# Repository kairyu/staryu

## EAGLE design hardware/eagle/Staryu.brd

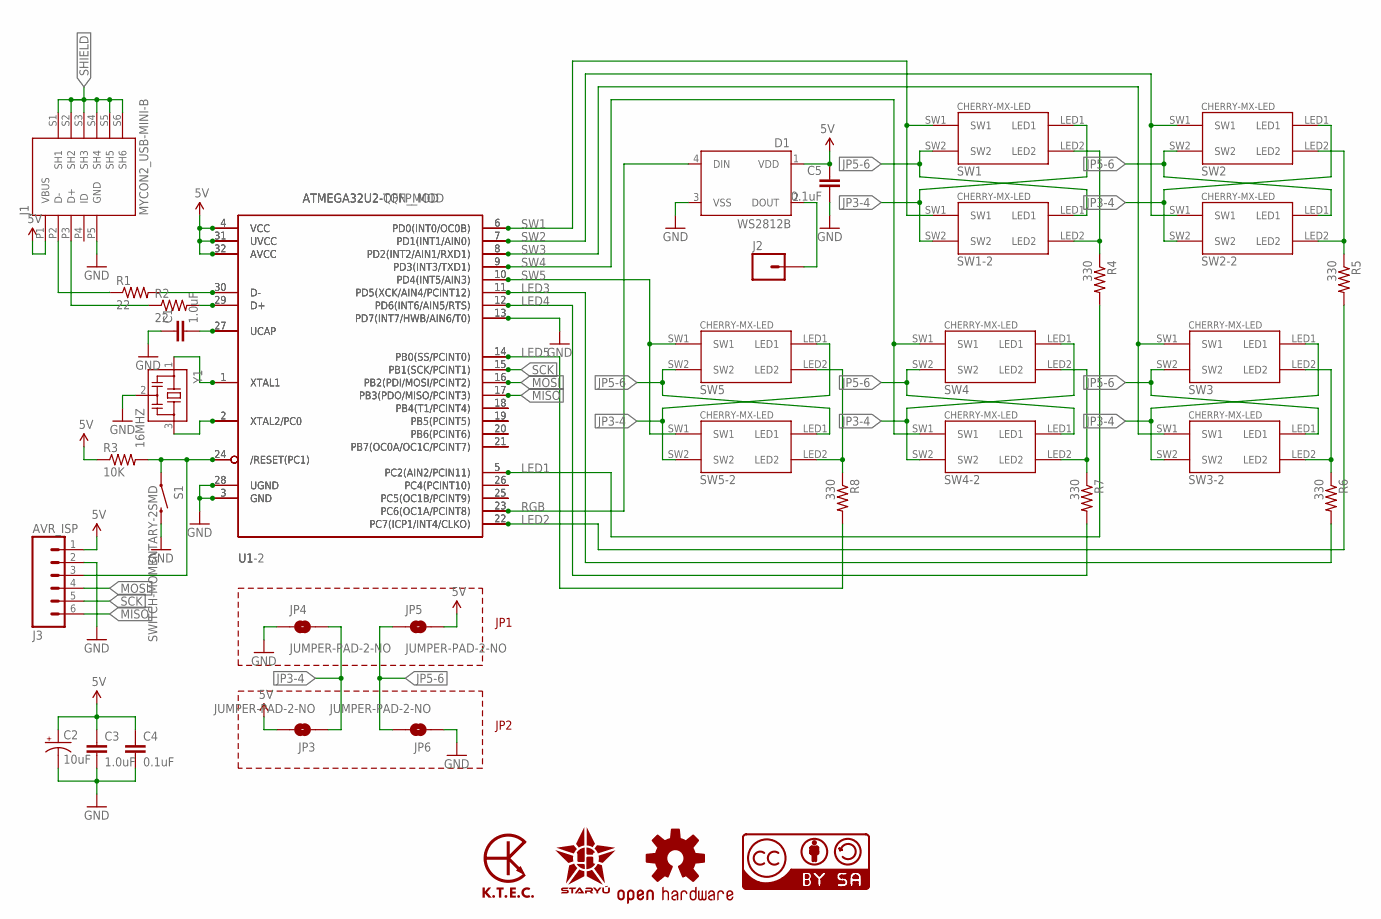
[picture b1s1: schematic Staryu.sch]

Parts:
C1, C3: 1.0uF; 0805-CAP
C2: 10uF; EIA3216
C4, C5: 0.1uF; 0805
D1: WS2812B; WS2812B_NOSILK
J1: MYCON2_USB-MINI-B; CON2_USB_MICRO_B_AT
J2: M01PTH_NO_SILK_YES_STOP; 1X01_NO_SILK
J3: AVR_ISP; 1X06_NO_SILK
JP3, JP4, JP5, JP6: JUMPER-PAD-2-NO; PAD-JUMPER-2-NO_NO_SILK
LOGO1: K.T.E.C._LOGO3_COPPER_EXP_S; K.T.E.C._LOGO3_COPPER_EXPOSED_S
LOGO2: STARYU_LOGO
LOGO3: OSHW_LOGOM_EXP; OSHW_LOGO_COPPER_EXPOSED_M
LOGO4: CC-BY-SANIX; CC-BY-SA_NIX
R1, R2: 22; 0805
R3: 10K; 0805
R4, R5, R6, R7, R8: 330; 0805
S1: SWITCH-MOMENTARY-2SMD; TACTILE-SWITCH-SMD
SW1, SW1-2, SW2, SW2-2, SW3, SW3-2, SW4, SW4-2, SW5, SW5-2: CHERRY-MX-LED-MOD
U1: ATMEGA32U2-TQFP_MOD; TQFP32-08_MOD
U1-2: ATMEGA32U2-QFN_MOD; QFN32_MOD
Y1: 16MHZ; CST

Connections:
5V: C2.A (+), C3.1, C4.1, C5.1, D1.1 (VDD), J1.P1 (VBUS), J3.1, JP3.2, JP5.2, R3.1, U1.4 (VCC), U1.31 (UVCC), U1.32 (AVCC), U1-2.4 (VCC), U1-2.31 (UVCC), U1-2.32 (AVCC)
GND: C1.1, C2.C (-), C3.2, C4.2, C5.2, D1.3 (VSS), J1.P5 (GND), J3.2, JP4.1, JP6.1, S1.3 (2), U1.3 (GND), U1.13 (PD7(INT7/HWB/AIN6/T0)), U1.28 (UGND), U1-2.3 (GND), U1-2.13 (PD7(INT7/HWB/AIN6/T0)), U1-2.28 (UGND), Y1.2
JP3-4: JP3.1, JP4.2, SW1.LED1, SW1-2.SW2, SW2.LED1, SW2-2.SW2, SW3.LED1, SW3-2.SW2, SW4.LED1, SW4-2.SW2, SW5.LED1, SW5-2.SW2
JP5-6: JP5.1, JP6.2, SW1.SW2, SW1-2.LED1, SW2.SW2, SW2-2.LED1, SW3.SW2, SW3-2.LED1, SW4.SW2, SW4-2.LED1, SW5.SW2, SW5-2.LED1
LED1: R4.2, U1.5 (PC2(AIN2/PCIN11)), U1-2.5 (PC2(AIN2/PCIN11))
LED2: R5.2, U1.22 (PC7(ICP1/INT4/CLKO)), U1-2.22 (PC7(ICP1/INT4/CLKO))
LED3: R6.2, U1.11 (PD5(XCK/AIN4/PCINT12)), U1-2.11 (PD5(XCK/AIN4/PCINT12))
LED4: R7.2, U1.12 (PD6(INT6/AIN5/RTS)), U1-2.12 (PD6(INT6/AIN5/RTS))
LED5: R8.2, U1.14 (PB0(SS/PCINT0)), U1-2.14 (PB0(SS/PCINT0))
MISO: J3.6, U1.17 (PB3(PDO/MISO/PCINT3)), U1-2.17 (PB3(PDO/MISO/PCINT3))
MOSI: J3.4, U1.16 (PB2(PDI/MOSI/PCINT2)), U1-2.16 (PB2(PDI/MOSI/PCINT2))
unnamed: R2.2, U1.29 (D+), U1-2.29 (D+)
unnamed: R1.2, U1.30 (D-), U1-2.30 (D-)
unnamed: J1.P2 (D-), R1.1
unnamed: J1.P3 (D+), R2.1
unnamed: U1.1 (XTAL1), U1-2.1 (XTAL1), Y1.1
unnamed: U1.2 (XTAL2/PC0), U1-2.2 (XTAL2/PC0), Y1.3
unnamed: C1.2, U1.27 (UCAP), U1-2.27 (UCAP)
unnamed: J3.3, R3.2, S1.1, U1.24 (/RESET(PC1)), U1-2.24 (/RESET(PC1))
unnamed: D1.2 (DOUT), J2.1
unnamed: R5.1, SW2.LED2, SW2-2.LED2
unnamed: R6.1, SW3.LED2, SW3-2.LED2
unnamed: R7.1, SW4.LED2, SW4-2.LED2
unnamed: R8.1, SW5.LED2, SW5-2.LED2
unnamed: U1.18 (PB4(T1/PCINT4)), U1-2.18 (PB4(T1/PCINT4))
unnamed: U1.19 (PB5(PCINT5)), U1-2.19 (PB5(PCINT5))
unnamed: U1.20 (PB6(PCINT6)), U1-2.20 (PB6(PCINT6))
unnamed: U1.21 (PB7(OC0A/OC1C/PCINT7)), U1-2.21 (PB7(OC0A/OC1C/PCINT7))
unnamed: U1.26 (PC4(PCINT10)), U1-2.26 (PC4(PCINT10))
unnamed: U1.25 (PC5(OC1B/PCINT9)), U1-2.25 (PC5(OC1B/PCINT9))
unnamed: R4.1, SW1.LED2, SW1-2.LED2
RGB: D1.4 (DIN), U1.23 (PC6(OC1A/PCINT8)), U1-2.23 (PC6(OC1A/PCINT8))
SCK: J3.5, U1.15 (PB1(SCK/PCINT1)), U1-2.15 (PB1(SCK/PCINT1))
SHIELD: J1.S1 (SH1), J1.S2 (SH2), J1.S3 (SH3), J1.S4 (SH4), J1.S5 (SH5), J1.S6 (SH6)
SW1: SW1.SW1, SW1-2.SW1, U1.6 (PD0(INT0/OC0B)), U1-2.6 (PD0(INT0/OC0B))
SW2: SW2.SW1, SW2-2.SW1, U1.7 (PD1(INT1/AIN0)), U1-2.7 (PD1(INT1/AIN0))
SW3: SW3.SW1, SW3-2.SW1, U1.8 (PD2(INT2/AIN1/RXD1)), U1-2.8 (PD2(INT2/AIN1/RXD1))
SW4: SW4.SW1, SW4-2.SW1, U1.9 (PD3(INT3/TXD1)), U1-2.9 (PD3(INT3/TXD1))
SW5: SW5.SW1, SW5-2.SW1, U1.10 (PD4(INT5/AIN3)), U1-2.10 (PD4(INT5/AIN3))

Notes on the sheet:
JP1
JP2

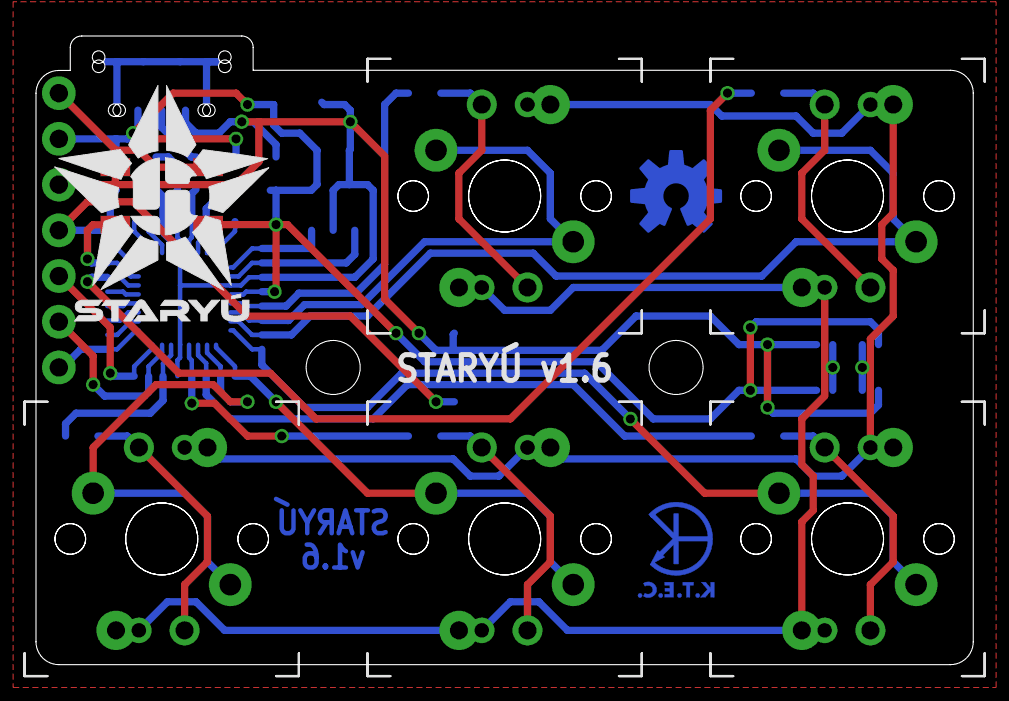
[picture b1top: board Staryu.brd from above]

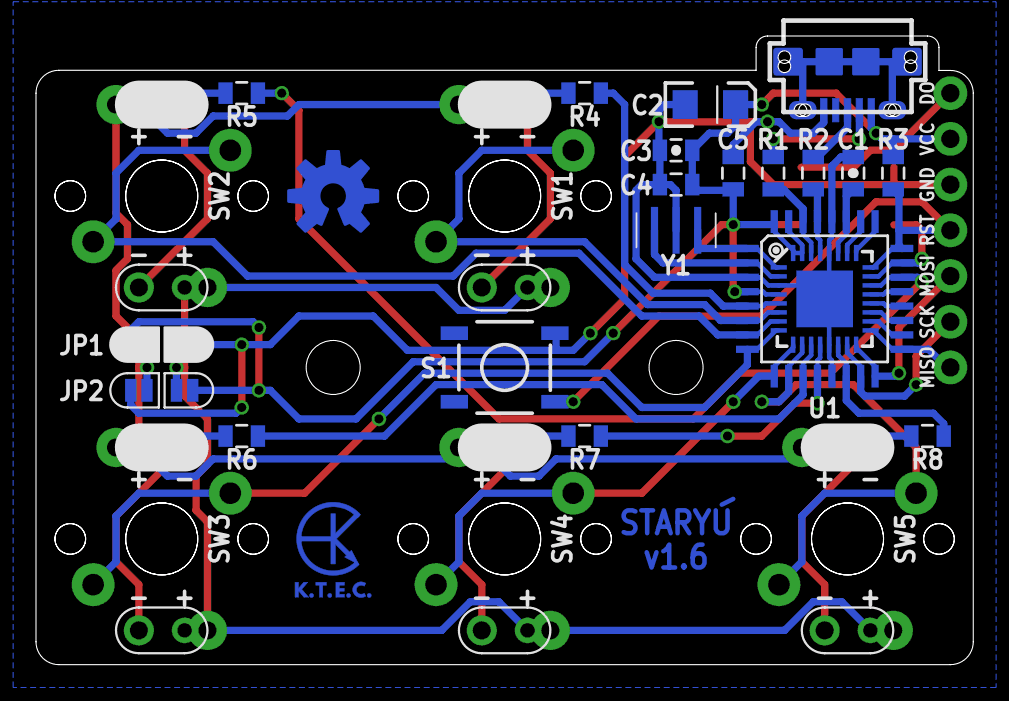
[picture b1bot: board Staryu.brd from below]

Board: 2 copper layers, 52.1 x 34.9 mm, 39 parts (24 on the bottom side), 39 nets.

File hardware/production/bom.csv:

"Part","Value","Device","Package","Description","PROD_ID","VALUE",
"C1","1.0uF","1.0UF-25V-+80/-20(0805)"","0805-CAP","CAP-11625","CAP-11625","1.0uF",
"C2","10uF","10UF-16V-10%(TANT)","EIA3216","CAP-00811","CAP-00811","10uF",
"C3","1.0uF","1.0UF-25V-+80/-20(0805)"","0805-CAP","CAP-11625","CAP-11625","1.0uF",
"C4","0.1uF","CAP0805","0805","Capacitor","","",
"C5","0.1uF","CAP0805","0805","Capacitor","","",
"D1","WS2812B","WS2812BNOSILK","WS2812B_NOSILK","WS2812B - Intelligent control LED integrated light source","","",
"J1","MYCON2_USB-MINI-B","MYCON2_USB-MINI-B","CON2_USB_MICRO_B_AT","","","",
"R1","22","RESISTOR0805-RES","0805","Resistor","","",
"R2","22","RESISTOR0805-RES","0805","Resistor","","",
"R3","10K","RESISTOR0805-RES","0805","Resistor","","",
"R4","330","RESISTOR0805-RES","0805","Resistor","","",
"R5","330","RESISTOR0805-RES","0805","Resistor","","",
"R6","330","RESISTOR0805-RES","0805","Resistor","","",
"R7","330","RESISTOR0805-RES","0805","Resistor","","",
"R8","330","RESISTOR0805-RES","0805","Resistor","","",
"S1","SWITCH-MOMENTARY-2SMD","SWITCH-MOMENTARY-2SMD","TACTILE-SWITCH-SMD","Various NO switches- pushbuttons, reed, etc","SWCH-08247","",
"SW1","CHERRY-MX-LED-MOD","CHERRY-MX-LED-MOD","CHERRY-MX-LED-MOD","Cherry MX series keyswitch with LED","","",
"SW1-2","CHERRY-MX-LED-MOD","CHERRY-MX-LED-MOD","CHERRY-MX-LED-MOD","Cherry MX series keyswitch with LED","","",
"SW2","CHERRY-MX-LED-MOD","CHERRY-MX-LED-MOD","CHERRY-MX-LED-MOD","Cherry MX series keyswitch with LED","","",
"SW2-2","CHERRY-MX-LED-MOD","CHERRY-MX-LED-MOD","CHERRY-MX-LED-MOD","Cherry MX series keyswitch with LED","","",
"SW3","CHERRY-MX-LED-MOD","CHERRY-MX-LED-MOD","CHERRY-MX-LED-MOD","Cherry MX series keyswitch with LED","","",
"SW3-2","CHERRY-MX-LED-MOD","CHERRY-MX-LED-MOD","CHERRY-MX-LED-MOD","Cherry MX series keyswitch with LED","","",
"SW4","CHERRY-MX-LED-MOD","CHERRY-MX-LED-MOD","CHERRY-MX-LED-MOD","Cherry MX series keyswitch with LED","","",
"SW4-2","CHERRY-MX-LED-MOD","CHERRY-MX-LED-MOD","CHERRY-MX-LED-MOD","Cherry MX series keyswitch with LED","","",
"SW5","CHERRY-MX-LED-MOD","CHERRY-MX-LED-MOD","CHERRY-MX-LED-MOD","Cherry MX series keyswitch with LED","","",
"SW5-2","CHERRY-MX-LED-MOD","CHERRY-MX-LED-MOD","CHERRY-MX-LED-MOD","Cherry MX series keyswitch with LED","","",
"U1","ATMEGA32U2-TQFP_MOD","ATMEGA32U2-TQFP_MOD","TQFP32-08_MOD","ATmega32u2","","",
"U1-2","ATMEGA32U2-QFN_MOD","ATMEGA32U2-QFN_MOD","QFN32_MOD","ATmega32u2","","",
"Y1","16MHZ","CSTCE16M0V53-R0","CST","Resonator","","",

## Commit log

2015-04-07 Modify project name and add license
2015-04-07 Import v1.0 PCB files and schematics
2015-04-07 Update eagle files and schematics to v1.2 - Change 3 LEDs on top side to WS2812B
2015-04-07 Import logo files plain.svg is a Plain SVG version for importing into eagle
2015-04-07 Update eagle files and schematics to v1.2 - Compact outline - Relocate LED and re-route circuits - Add logos
2015-04-07 Add production files for v1.2
2015-04-07 Add logo to README
2015-05-11 Update eagle files and schematics to v1.3 - Contract outline even more - Change logo to exposing copper - Change footprint of resonator to be easier to solder
2015-05-11 Add test firmware for v1.3 hardware
2015-05-12 Add a simple case
2016-09-02 Update hardware to v1.4 - Support both of ATMEGA32U2-AU (32-TQFP) and ATMEGA32U2-MU (32-QFN) - Support both of normal and reverse mounting switch (selected by jumper) - Replace Micro USB connector wi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
2016-09-02 Update firmware to support v1.4 hardware - kairyu/tkg-firmware@4813e17f699e10bb9ae2aeee886a0f251f69082e
2016-09-02 Add more cases for staryu
2017-03-15 Update hardware to v1.5 - Improve jumpers for selecting switch mounting - Change logo
2017-03-15 Update hardware to v1.6 - Optimize routing under ATMEGA32U2-MU to avoid short by thermal pad
2017-04-14 fix typo on bom.csv (#1)
    * fix typo on bom.csv
    * typo

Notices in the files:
parts and their libraries:
SparkFun-Capacitors: Licensing: Creative Commons ShareAlike 4.0 International - https://creativecommons.org/licenses/by-sa/4.0
cc-by-sa: All hardware is licensed under the Creative Commons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
